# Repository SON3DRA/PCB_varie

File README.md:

# PCB_varie
Pcb di circuiti vari

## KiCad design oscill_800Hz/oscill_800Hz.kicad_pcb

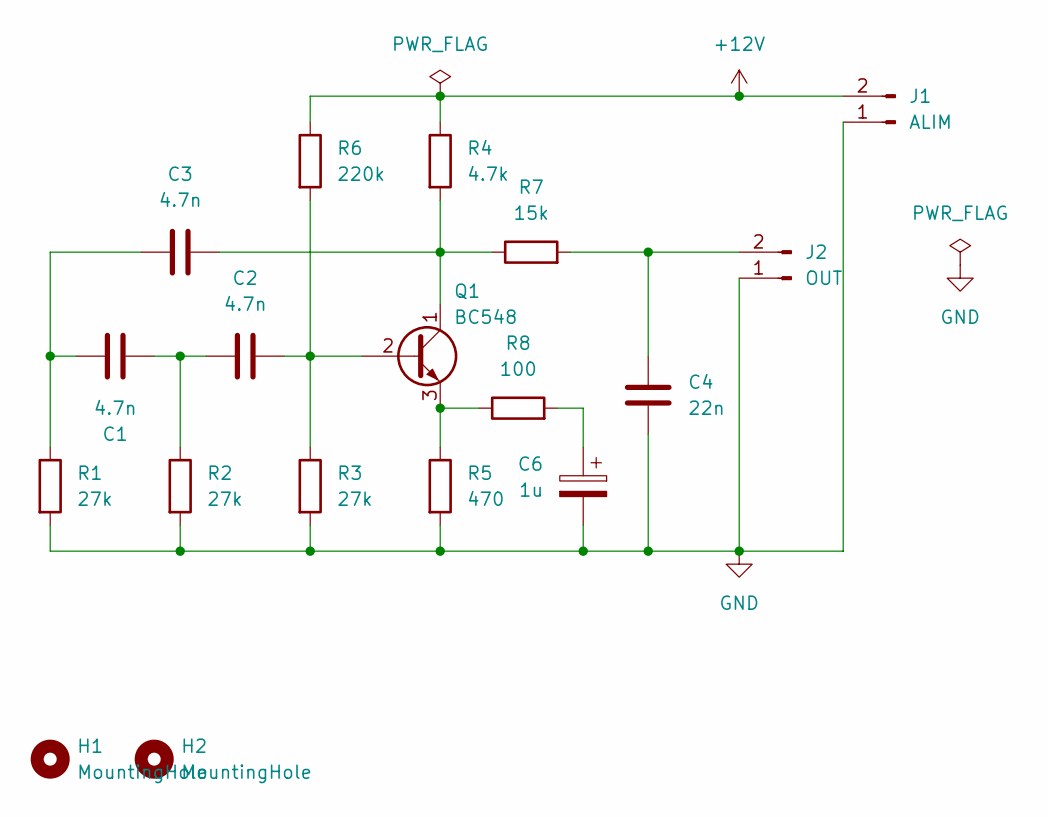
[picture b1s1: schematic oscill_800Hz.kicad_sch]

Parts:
C1, C2, C3: 4.7n; C_Disc_D4.7mm_W2.5mm_P5.00mm
C4: 22n; C_Disc_D4.7mm_W2.5mm_P5.00mm
C6: 1u; CP_Radial_D5.0mm_P2.50mm
H1, H2: MountingHole; MountingHole_2.2mm_M2_Pad
J1: ALIM; PinHeader_1x02_P2.54mm_Vertical
J2: OUT; PinHeader_1x02_P2.54mm_Vertical
Q1: BC548; TO-92_Inline_Wide
R1, R2, R3: 27k; R_Axial_DIN0207_L6.3mm_D2.5mm_P10.16mm_Horizontal
R4: 4.7k; R_Axial_DIN0207_L6.3mm_D2.5mm_P10.16mm_Horizontal
R5: 470; R_Axial_DIN0207_L6.3mm_D2.5mm_P10.16mm_Horizontal
R6: 220k; R_Axial_DIN0207_L6.3mm_D2.5mm_P10.16mm_Horizontal
R7: 15k; R_Axial_DIN0207_L6.3mm_D2.5mm_P10.16mm_Horizontal
R8: 100; R_Axial_DIN0207_L6.3mm_D2.5mm_P10.16mm_Horizontal

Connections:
+12V: J1.2, R4.1, R6.1
GND: C4.1, C6.2, J1.1, J2.1, R1.2, R2.2, R3.2, R5.2
unnamed: C1.1, C3.1, R1.1
unnamed: C1.2, C2.1, R2.1
unnamed: C6.1, R8.2
unnamed: C4.2, J2.2, R7.2
unnamed: C2.2, Q1.2 (B), R3.1, R6.2
unnamed: C3.2, Q1.1 (C), R4.2, R7.1
unnamed: Q1.3 (E), R5.1, R8.1

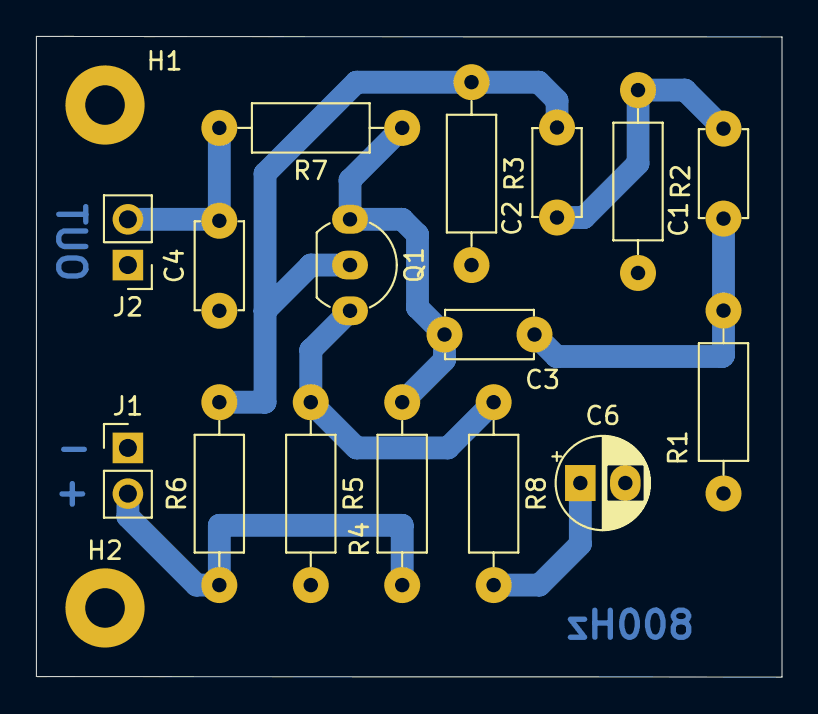
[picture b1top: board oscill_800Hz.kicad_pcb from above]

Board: 2 copper layers, 41.4 x 35.6 mm, 18 parts (0 on the bottom side), 9 nets.

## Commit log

2024-11-16 Add files via upload
    Oscillatore 800Hz tipo T-Twin ad 1 transistor
